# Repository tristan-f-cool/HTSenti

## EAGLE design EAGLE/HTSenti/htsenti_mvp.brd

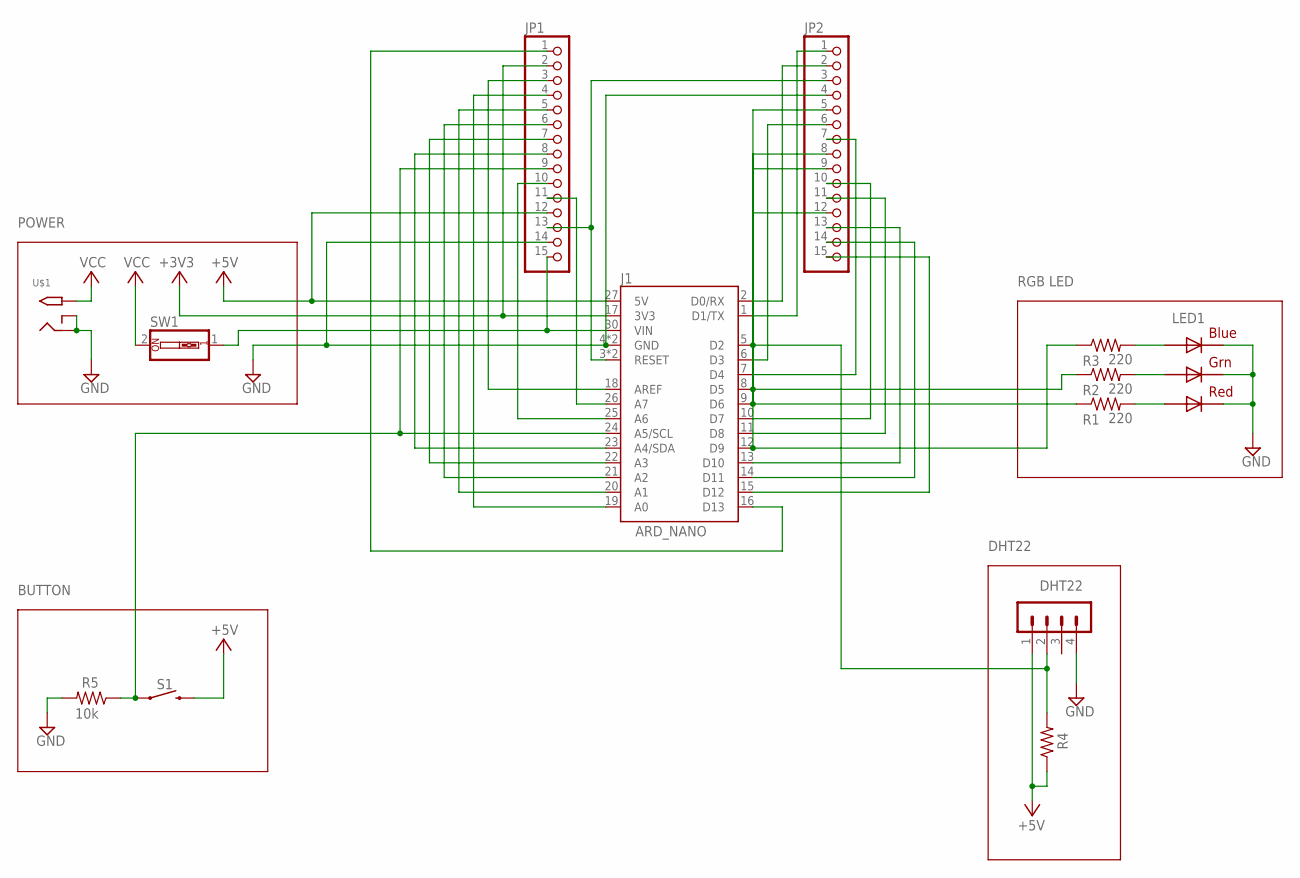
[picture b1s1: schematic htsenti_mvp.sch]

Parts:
DHT22: MA04-1
J1: NANO_FOOTPRINT; NANO
JP1, JP2: PINHD-1X15; 1X15
LED1: RGBLED5050
R1, R2, R3: 220; 0603
R4: R-US_M0805; M0805
R5: 10k; M0805
S1: MOMENTARY-SWITCH-SPST-SMD-6.2MM-TALL; TACTILE_SWITCH_SMD_6.2MM_TALL
SW1: SW_DIP-1; EDG-01
U$1: 2.1MMJACKSMT; DCJACK_2MM_SMT

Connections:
+3V3: J1.17 (3V3), JP1.2
+5V: DHT22.1, J1.27 (5V), JP1.12, R4.1, S1.B2 (2)
GND: DHT22.4, J1.4 (GND), J1.29 (GND), JP1.14, JP2.4, LED1.4 (BLUE_C), LED1.5 (RED_C), LED1.6 (GREEN_C), R5.2, U$1.GND (RING), U$1.GNDBREAK (RING_SW)
unnamed: LED1.2 (RED_A), R1.2
unnamed: LED1.1 (GREEN_A), R2.2
unnamed: LED1.3 (BLUE_A), R3.2
unnamed: J1.9 (D6), JP2.9, R1.1
unnamed: J1.8 (D5), JP2.8, R2.1
unnamed: J1.12 (D9), JP2.12, R3.1
unnamed: DHT22.2, J1.5 (D2), JP2.5, R4.2
unnamed: J1.24 (A5/SCL), JP1.9, R5.1, S1.A2 (1)
unnamed: J1.1 (D1/TX), JP2.1
unnamed: J1.30 (VIN), JP1.15, SW1.1
unnamed: J1.2 (D0/RX), JP2.2
unnamed: J1.3 (RESET), J1.28 (RESET), JP1.13, JP2.3
unnamed: J1.6 (D3), JP2.6
unnamed: J1.7 (D4), JP2.7
unnamed: J1.10 (D7), JP2.10
unnamed: J1.11 (D8), JP2.11
unnamed: J1.13 (D10), JP2.13
unnamed: J1.14 (D11), JP2.14
unnamed: J1.15 (D12), JP2.15
unnamed: J1.16 (D13), JP1.1
unnamed: J1.18 (AREF), JP1.3
unnamed: J1.19 (A0), JP1.4
unnamed: J1.20 (A1), JP1.5
unnamed: J1.21 (A2), JP1.6
unnamed: J1.22 (A3), JP1.7
unnamed: J1.23 (A4/SDA), JP1.8
unnamed: J1.25 (A6), JP1.10
unnamed: J1.26 (A7), JP1.11
VCC: SW1.2, U$1.PWR2 (TIP)

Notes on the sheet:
RGB LED
DHT22
ARD_NANO
POWER
BUTTON

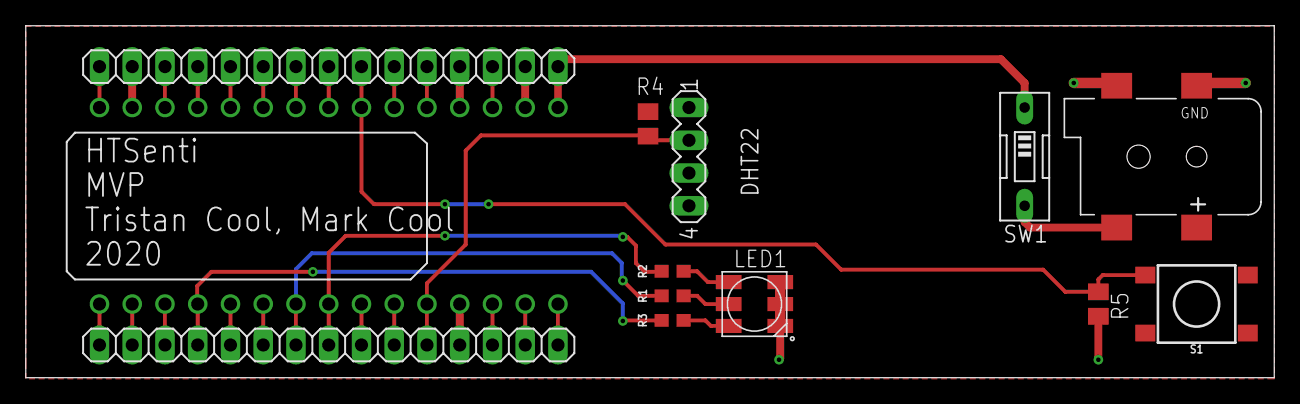
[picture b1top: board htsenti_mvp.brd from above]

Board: 2 copper layers, 96.8 x 27.3 mm, 13 parts (1 on the bottom side), 32 nets.

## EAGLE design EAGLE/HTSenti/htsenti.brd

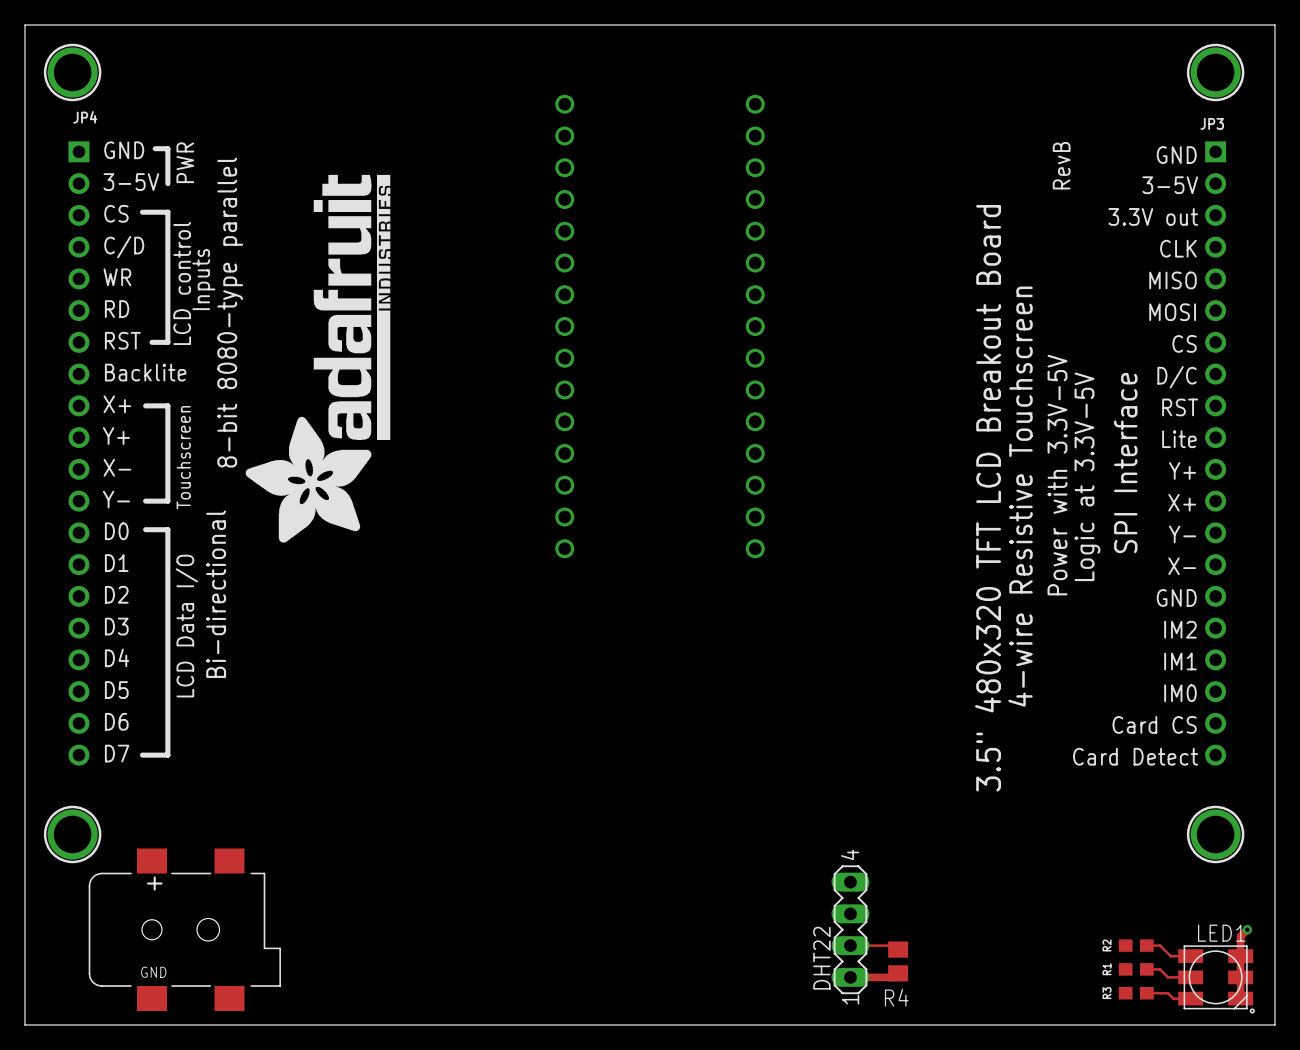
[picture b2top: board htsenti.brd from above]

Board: 2 copper layers, 100.0 x 80.0 mm, 15 parts (0 on the bottom side), 10 nets.

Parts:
DHT22: MA04-1
J1: NANO_FOOTPRINT; NANO
JP3, JP4: 1X20_ROUND
LED1: RGBLED5050
R1, R2, R3: 220; 0603
R4: M0805
U$1: 2.1MMJACKSMT; DCJACK_2MM_SMT
U$2, U$3, U$4, U$5: MOUNTINGHOLE3.0THIN; MOUNTINGHOLE_3.0_PLATEDTHIN
U$6: ADAFRUIT_TEXT_30MM

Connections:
+5V: DHT22.1, J1.27, R4.1
GND: DHT22.4, J1.4, J1.29, LED1.4, LED1.5, LED1.6, U$1.GND, U$1.GNDBREAK
unnamed: LED1.2, R1.2
unnamed: LED1.1, R2.2
unnamed: LED1.3, R3.2
unnamed: J1.9, R1.1
unnamed: J1.8, R2.1
unnamed: J1.12, R3.1
unnamed: DHT22.2, J1.5, R4.2
VCC: J1.30, U$1.PWR2

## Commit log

2020-09-09 initial commit - added Arduino sensor libraries
2020-09-09 added Eagle libraries
2020-09-09 added Fritizing bins
2020-09-09 Arduino program - initial DHT22 functionality and print
2020-09-09 added initial Fritzing breadboard and perfboard design
2020-09-09 removed Arduino code from PCB branch
2020-09-09 MVP perf and proto-board design
2020-09-09 re-added original Arduino code after merge
2020-09-10 added button functionality for heat-index for MVP
2020-09-24 added basic RGB LED functionality for button and start-up colours
2020-09-27 added error and start-up LED sequences
2020-09-27 imported Adafruit 2050 TFT Eagle schematic +board to create simplified Design Block
2020-09-27 created Eagle project, schematic and board - TODO
2020-10-01 correction in MVP proto-board wiring
2020-10-08 added RGB LED heat index corrected temperature function
2020-10-08 folder re-structure for MVP merge
2020-10-12 folder restructure
2020-10-12 MVP PCB
2020-10-12 MVP PCB CAM files

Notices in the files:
parts and their libraries:
SparkFun-Boards: Licensing: Creative Commons ShareAlike 4.0 International - https://creativecommons.org/licenses/by-sa/4.0
